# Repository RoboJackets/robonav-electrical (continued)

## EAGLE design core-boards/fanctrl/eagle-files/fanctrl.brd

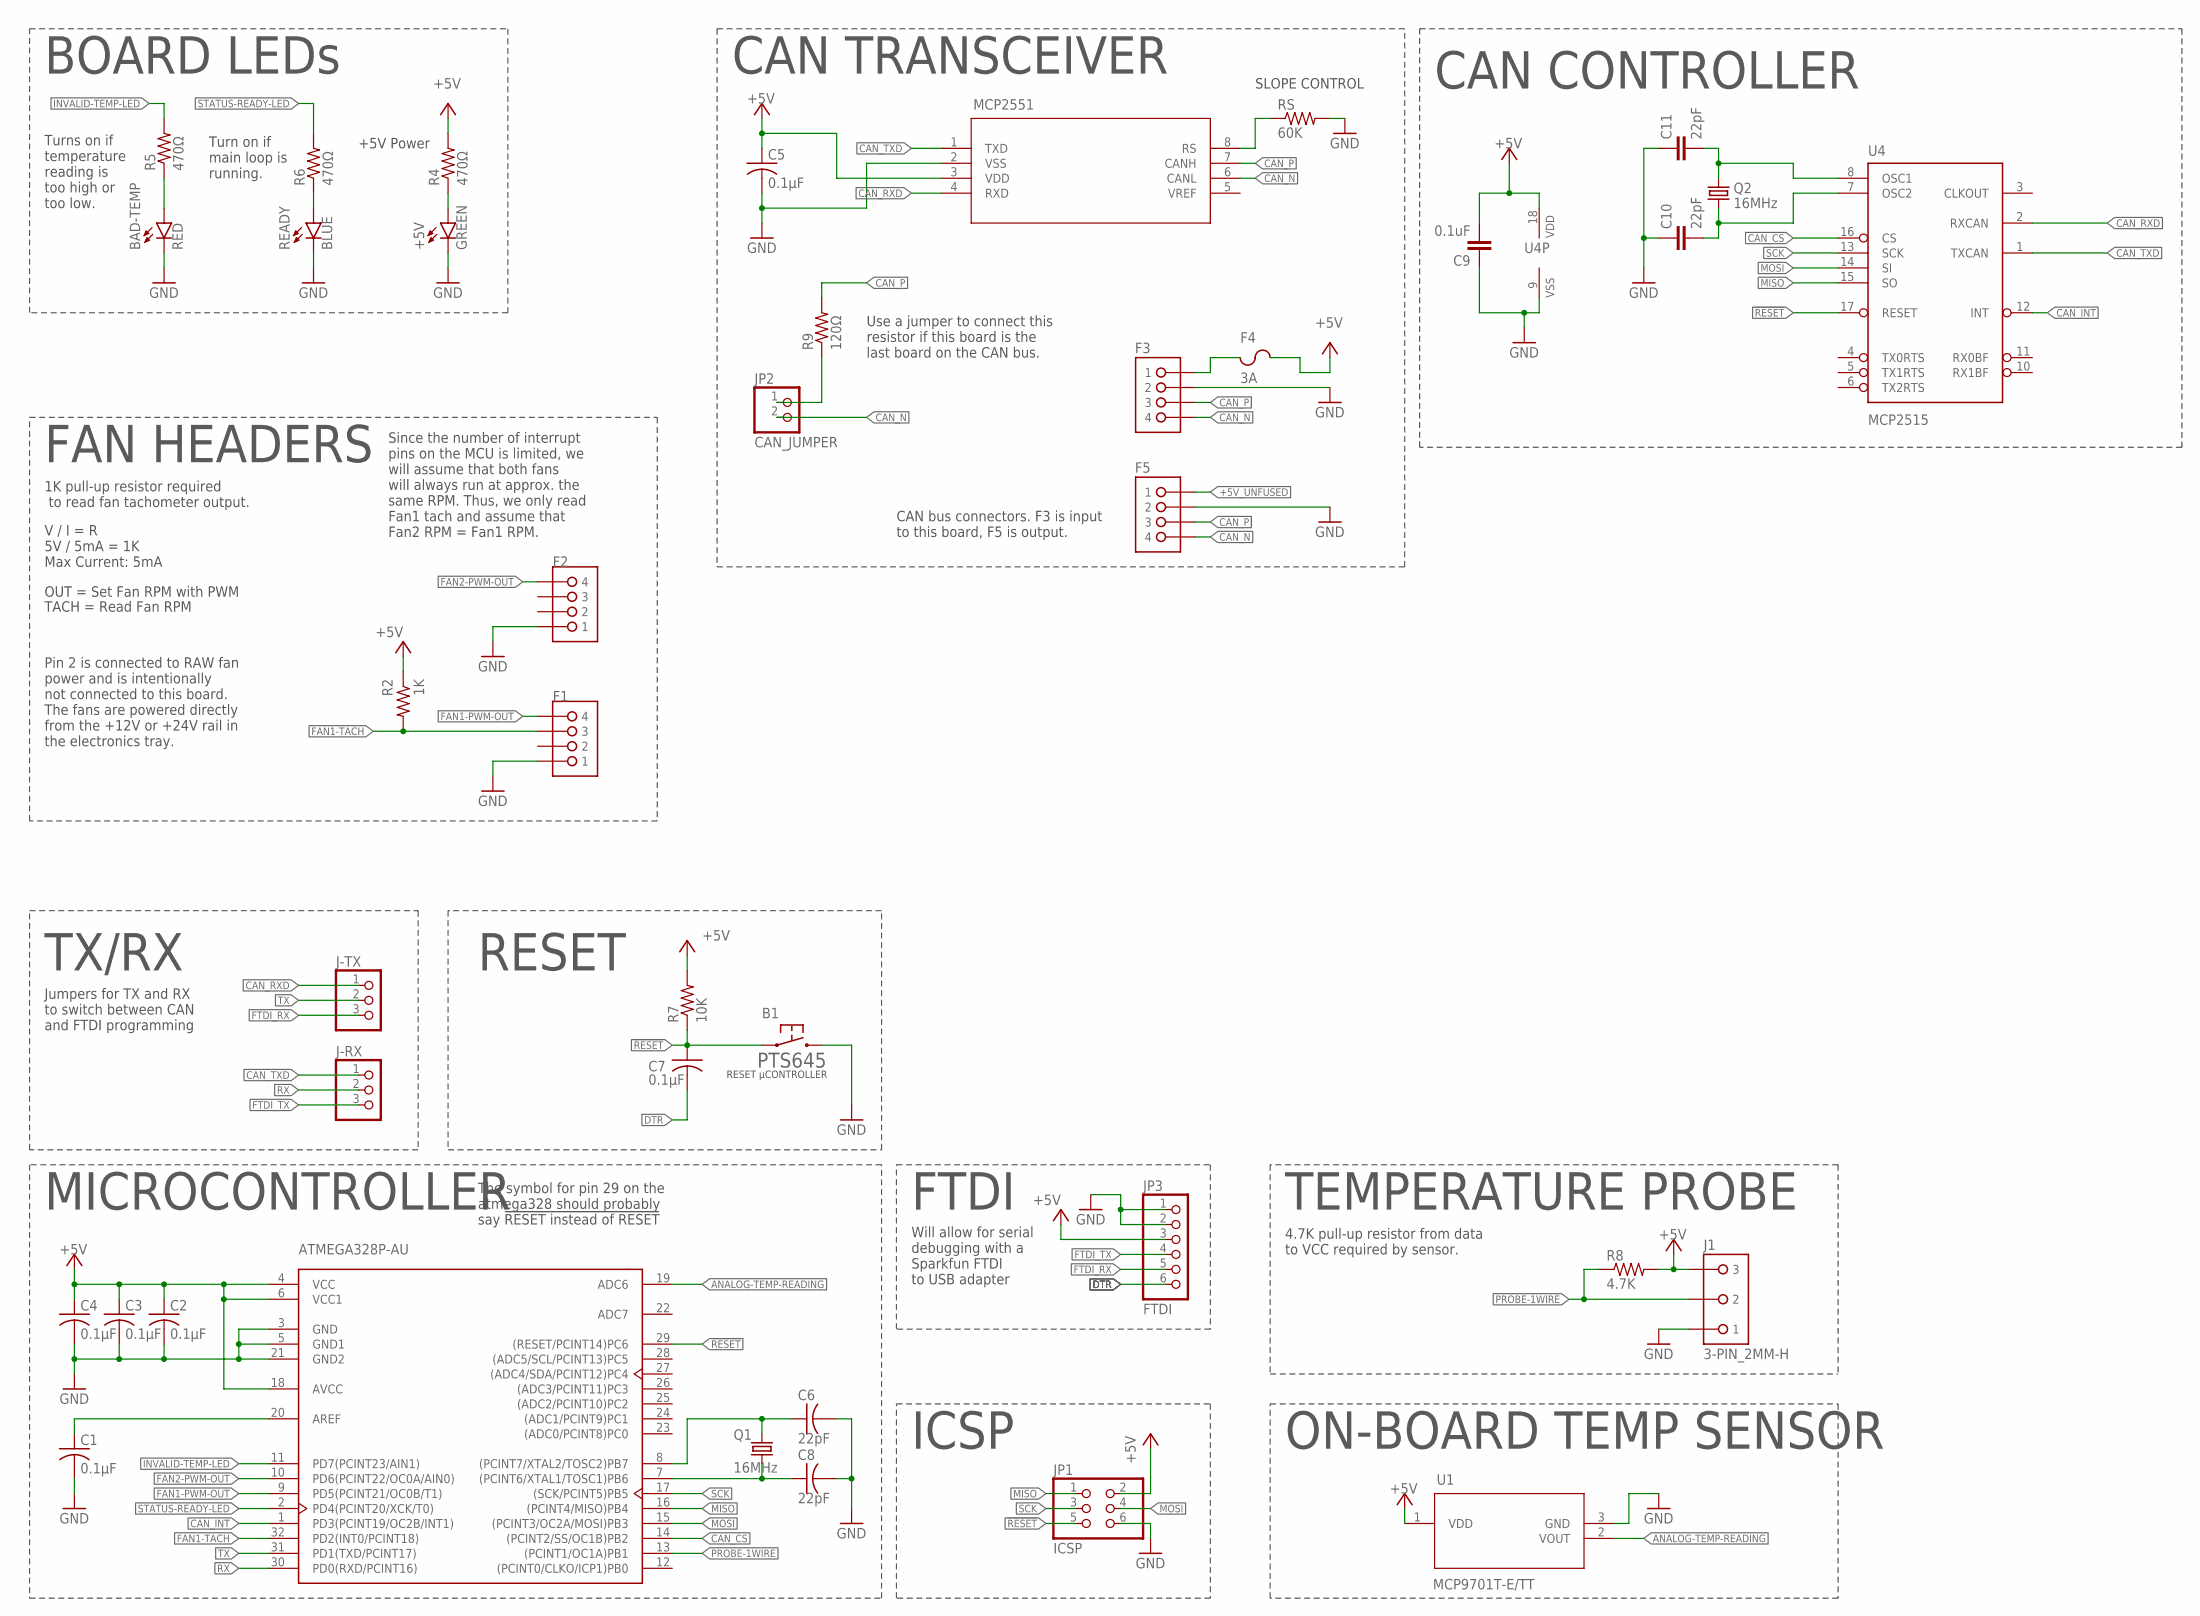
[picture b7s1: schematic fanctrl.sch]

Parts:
+5V: GREEN; CHIPLED_0603
ATMEGA328: ATMEGA328P-AU; TQFP-32
B1: PTS645
BAD-TEMP: RED; CHIPLED_0603
C1, C2, C3, C4, C5, C7: 0.1µF; C0603
C6, C8: 22pF; C0603
C9: 0.1uF; 0603-CAP
C10, C11: 22pF; 0603-CAP
F1, F2, F3, F5: 4-PIN_2MM-H; 2MM-4-H
F4: 3A; F1206
J1: 3-PIN_2MM-H; 2MM-3-H
J-RX: PINHD-1X3; 1X03
J-TX: PINHD-1X3; 1X03
JP1: ICSP; 2X03
JP2: CAN_JUMPER; 1X02
JP3: FTDI; 1X06/90
MCP2551: MCP2551T-I/SN; SOIC8-N_MC
Q1, Q2: 16MHz; CRYSTAL-SMD-5X3
R2: 1K; R0603
R4, R5, R6: 470Ω; R0603
R7: 10K; R0603
R8: 4.7K; R0603
R9: 120Ω; R0603
READY: BLUE; CHIPLED_0603
RS: 60K; R0603
U1: MCP9701T-E/TT; SOT-23_MC
U4: MCP2515; SO-18W

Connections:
!RESET: ATMEGA328.29 ((RESET/PCINT14)PC6), B1.P$1 (1), B1.P$2 (1), C7.1, JP1.5, R7.1, U4.17 (RESET)
+5V: ATMEGA328.4 (VCC), ATMEGA328.6 (VCC1), ATMEGA328.18 (AVCC), C2.1, C3.1, C4.1, C5.1, C9.2, F4.2, JP1.2, JP3.3, MCP2551.3 (VDD), R2.1, R4.2, R7.2, U1.1 (VDD), U4.18 (VDD)
+5V_UNFUSED: F3.1, F4.1, F5.1
ANALOG-TEMP-READING: ATMEGA328.19 (ADC6), U1.2 (VOUT)
AREF: ATMEGA328.20 (AREF), C1.1
CAN_CS: ATMEGA328.14 ((PCINT2/SS/OC1B)PB2), U4.16 (CS)
CAN_INT: ATMEGA328.1 (PD3(PCINT19/OC2B/INT1)), U4.12 (INT)
CAN_N: F3.4, F5.4, JP2.2, MCP2551.6 (CANL)
CAN_P: F3.3, F5.3, MCP2551.7 (CANH), R9.2
CAN_RS: MCP2551.8 (RS), RS.1
CAN_RXD: J-TX.1, MCP2551.4 (RXD), U4.2 (RXCAN)
CAN_TXD: J-RX.1, MCP2551.1 (TXD), U4.1 (TXCAN)
DTR: C7.2, JP3.6
FAN1-PWM-OUT: ATMEGA328.9 (PD5(PCINT21/OC0B/T1)), F1.4
FAN1-TACH: ATMEGA328.32 (PD2(INT0/PCINT18)), F1.3, R2.2
FAN2-PWM-OUT: ATMEGA328.10 (PD6(PCINT22/OC0A/AIN0)), F2.4
FTDI_RX: J-TX.3, JP3.5
FTDI_TX: J-RX.3, JP3.4
GND: +5V.C, ATMEGA328.3 (GND), ATMEGA328.5 (GND1), ATMEGA328.21 (GND2), B1.P$3 (2), B1.P$4 (2), BAD-TEMP.C, C1.2, C2.2, C3.2, C4.2, C5.2, C6.2, C8.2, C9.1, C10.1, C11.1, F1.1, F2.1, F3.2, F5.2, J1.1, JP1.6, JP3.1, JP3.2, MCP2551.2 (VSS), READY.C, RS.2, U1.3 (GND), U4.9 (VSS)
INVALID-TEMP-LED: ATMEGA328.11 (PD7(PCINT23/AIN1)), R5.2
MISO: ATMEGA328.16 ((PCINT4/MISO)PB4), JP1.1, U4.15 (SO)
MOSI: ATMEGA328.15 ((PCINT3/OC2A/MOSI)PB3), JP1.4, U4.14 (SI)
unnamed: ATMEGA328.7 ((PCINT6/XTAL1/TOSC1)PB6), C8.1, Q1.1
unnamed: J1.3, R8.2
unnamed: +5V.A, R4.1
unnamed: BAD-TEMP.A, R5.1
unnamed: R6.1, READY.A
unnamed: ATMEGA328.8 ((PCINT7/XTAL2/TOSC2)PB7), C6.1, Q1.3 (2)
unnamed: C11.2, Q2.3 (2), U4.8 (OSC1)
unnamed: C10.2, Q2.1, U4.7 (OSC2)
PROBE-1WIRE: ATMEGA328.13 ((PCINT1/OC1A)PB1), J1.2, R8.1
RX: ATMEGA328.30 (PD0(RXD/PCINT16)), J-RX.2
R_JUMPER: JP2.1, R9.1
SCK: ATMEGA328.17 ((SCK/PCINT5)PB5), JP1.3, U4.13 (SCK)
STATUS-READY-LED: ATMEGA328.2 (PD4(PCINT20/XCK/T0)), R6.2
TX: ATMEGA328.31 (PD1(TXD/PCINT17)), J-TX.2

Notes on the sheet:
MICROCONTROLLER
BOARD LEDs
RESET
CAN TRANSCEIVER
FAN HEADERS
TEMPERATURE PROBE
ON-BOARD TEMP SENSOR
4.7K pull-up resistor from data to VCC required by sensor.
1K pull-up resistor required to read fan tachometer output.
The symbol for pin 29 on the atmega328 should probably say !RESET instead of RESET
V / I = R 5V / 5mA = 1K Max Current: 5mA
ICSP
OUT = Set Fan RPM with PWM
TACH = Read Fan RPM
Use a jumper to connect this resistor if this board is the last board on the CAN bus.
CAN bus connectors. F3 is input to this board, F5 is output.
Pin 2 is connected to RAW fan power and is intentionally not connected to this board. The fans are powered directly from the +12V or +24V rail in the electronics tray.
+5V Power
Turns on if temperature reading is too high or too low.
Turn on if main loop is running.
FTDI
SLOPE CONTROL
TX/RX
CAN CONTROLLER
Jumpers for TX and RX to switch between CAN and FTDI programming
Will allow for serial debugging with a Sparkfun FTDI to USB adapter
Since the number of interrupt pins on the MCU is limited, we will assume that both fans will always run at approx. the same RPM. Thus, we only read Fan1 tach and assume that Fan2 RPM = Fan1 RPM.

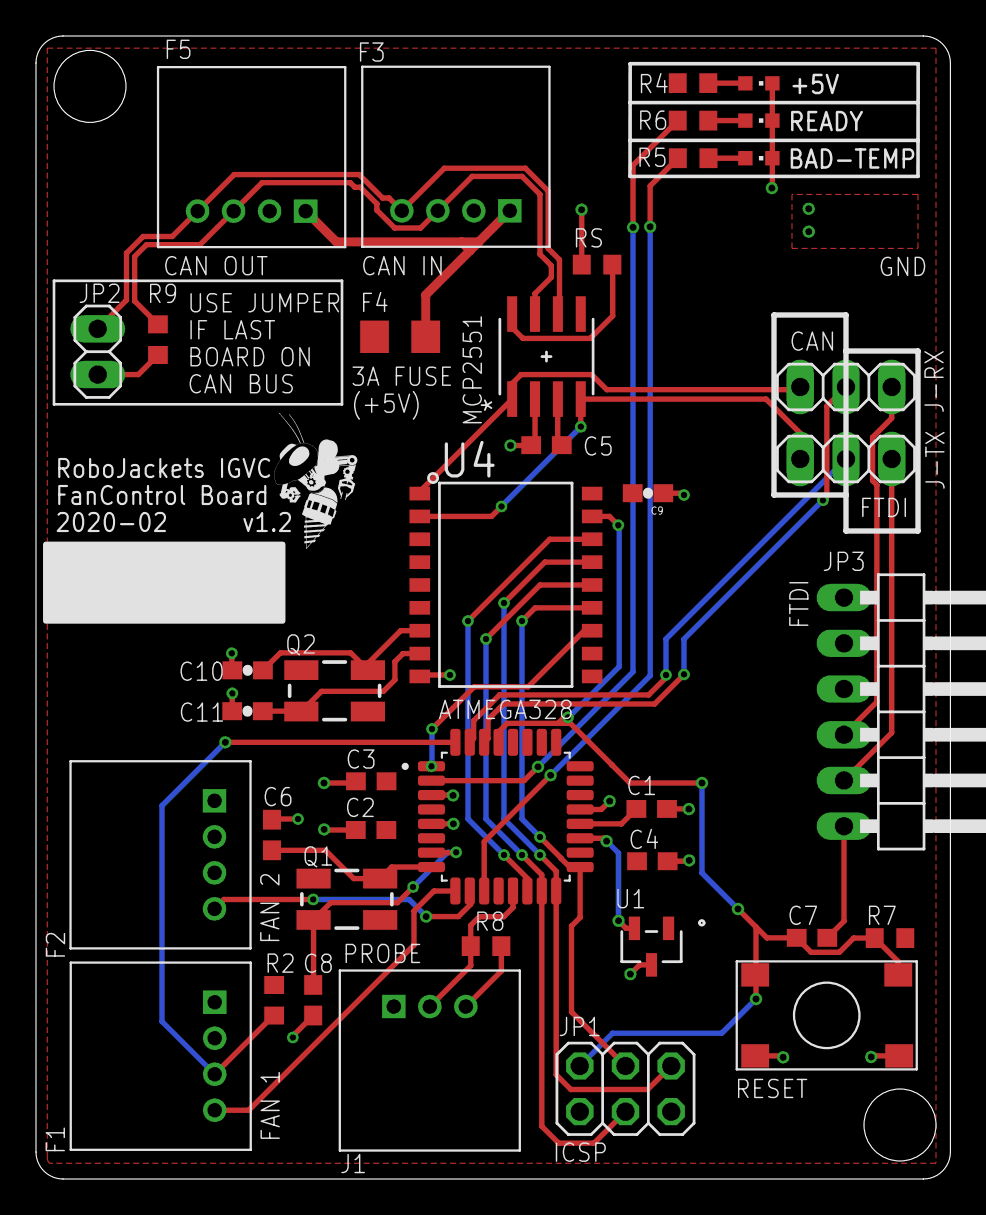
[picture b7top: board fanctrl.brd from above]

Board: 2 copper layers, 50.8 x 63.5 mm, 41 parts (0 on the bottom side), 36 nets.

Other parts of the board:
U$1: ROBOBUZZ_0.4X

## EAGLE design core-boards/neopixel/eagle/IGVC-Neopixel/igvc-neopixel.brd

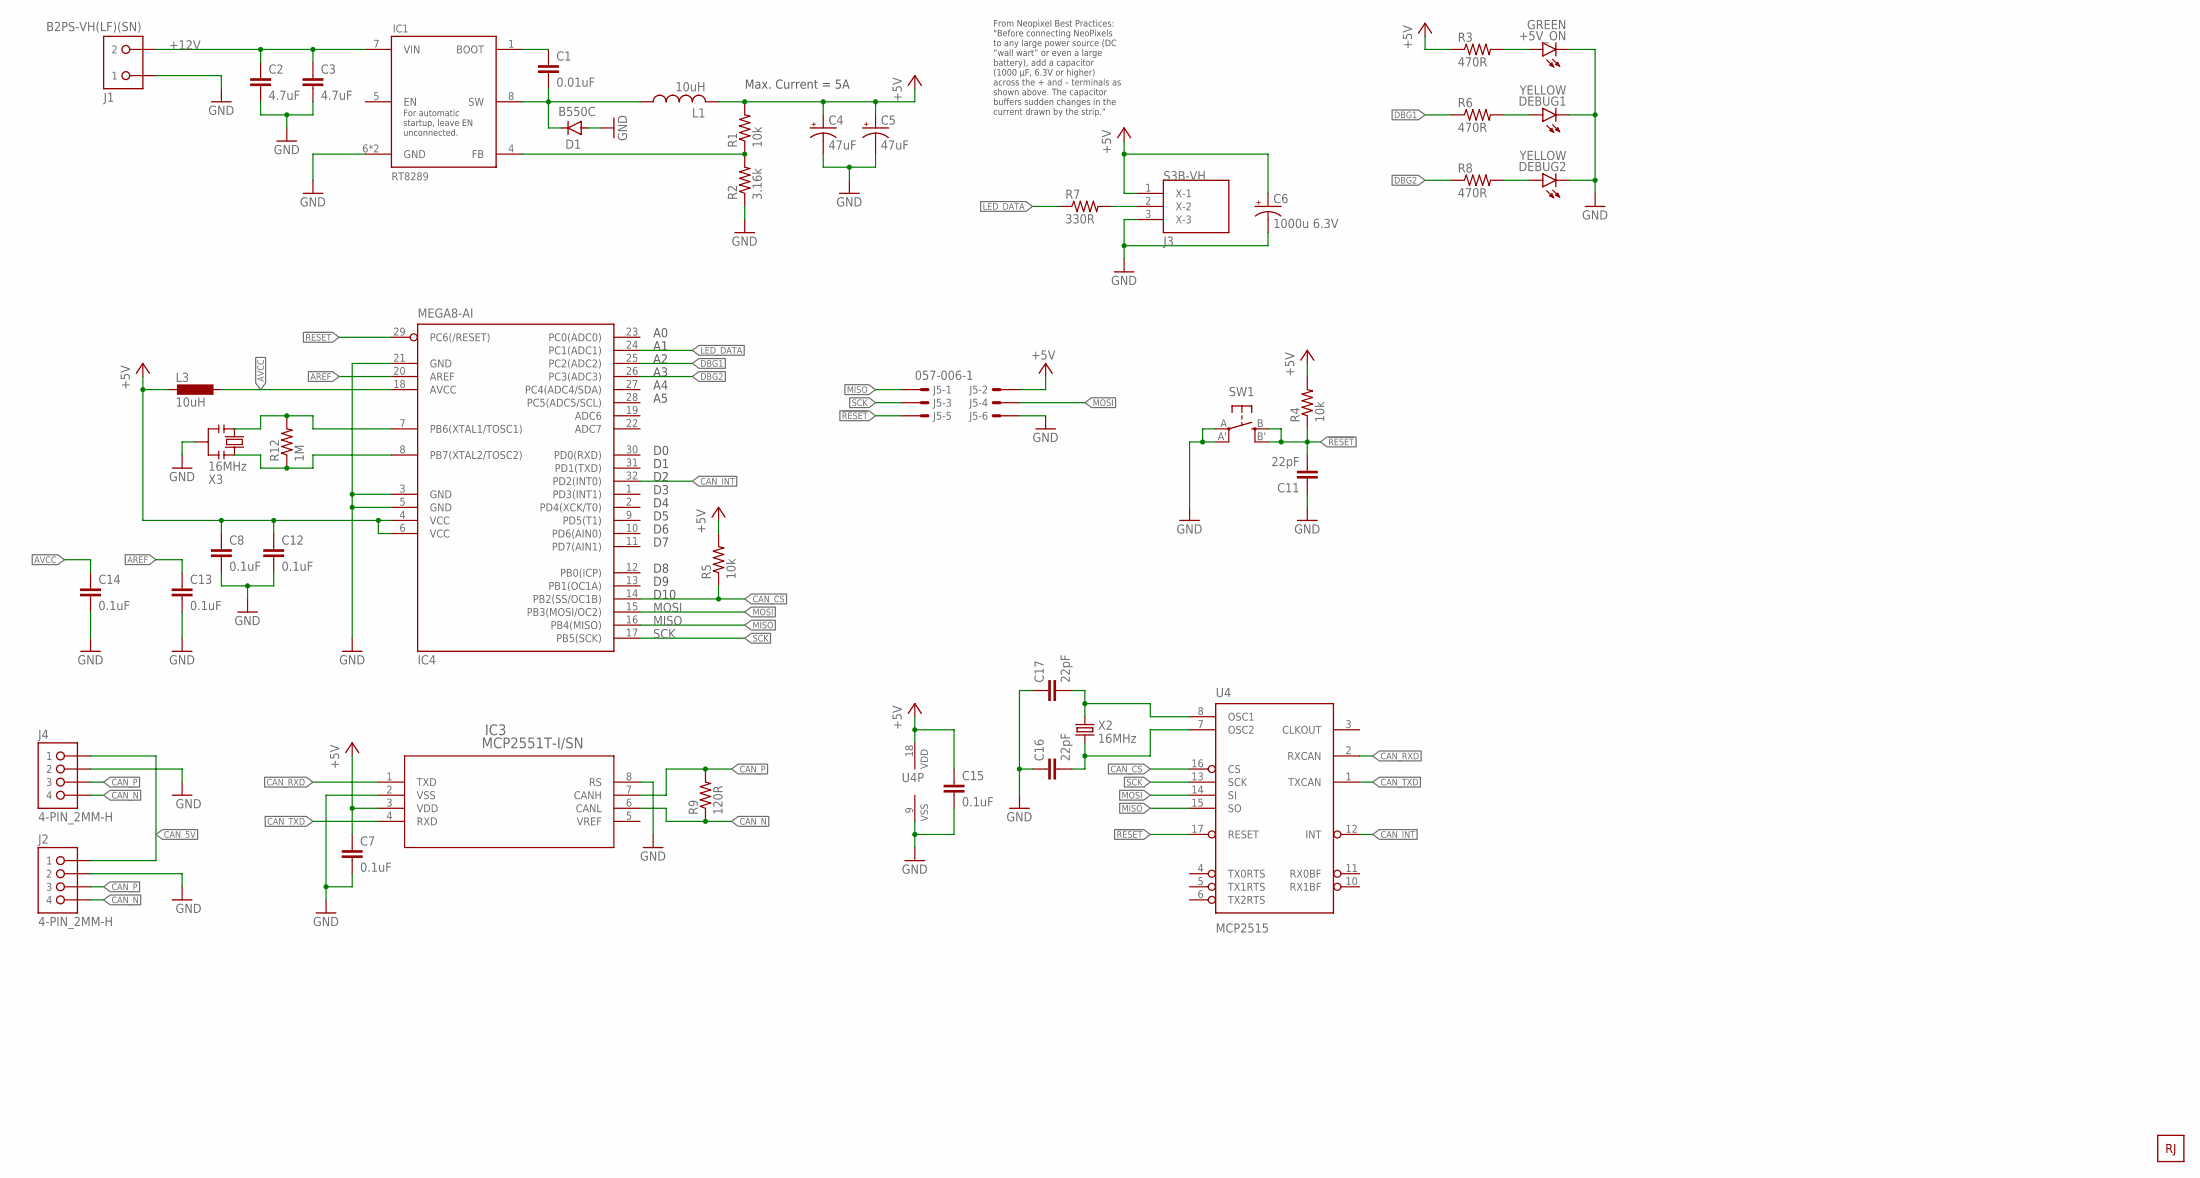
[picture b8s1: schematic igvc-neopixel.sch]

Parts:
+5V_ON: GREEN; CHIP-LED0805; DIGIKEY 732-4982-1-ND
C1: 0.01uF; C0603; DIGIKEY 311-1572-1-ND
C2, C3: 4.7uF; C1206; DIGIKEY 1276-3178-1-ND
C4, C5: 47uF; E5-10,5; DIGIKEY PCE3753CT-ND
C6: 1000u 6.3V; E5-10,5; DIGIKEY 493-2160-1-ND
C7, C8, C12, C13, C14: 0.1uF; C0603; DIGIKEY 399-1099-1-ND
C11: 22pF; C0603; DIGIKEY 311-3952-1-ND
C15: 0.1uF; C0603
C16, C17: 22pF; C0603; DIGIKEY 399-1099-1-ND
D1: B550C; SMC; DIGIKEY B550C-FDICT-ND
DEBUG1, DEBUG2: YELLOW; CHIP-LED0805; DIGIKEY 732-4987-1-ND
IC1: RT8289; SOIC8_EP; DIGIKEY 1028-1046-1-ND
IC3: MCP2551T-I/SN; SOIC8-N_MC; DIGIKEY MCP2551T-I/SNCT-ND
IC4: MEGA8-AI; TQFP32-08; DIGIKEY ATMEGA328P-AURCT-ND
J1: B2PS-VH(LF)(SN); B2PS-CENTERED
J2, J4: 4-PIN_2MM-H; 2MM-4-H
J3: S3B-VH; DIGIKEY 455-1649-ND
J5: 057-006-1; DIGIKEY 3M15451-ND
L1: 10uH; SRR1208; DIGIKEY SRR1208-100MLCT-ND
L3: 10uH; 0805; DIGIKEY 490-1053-1-ND
R1, R4: 10k; R0603; DIGIKEY RNCP0603FTD10K0CT-ND
R2: 3.16k; R0603; DIGIKEY RMCF0603FT3K16CT-ND
R3, R6, R8: 470R; R0603; DIGIKEY RMCF0603JT470RCT-ND
R5: 10k; R0603
R7: 330R; R0603; DIGIKEY RMCF0603JT330RCT-ND
R9: 120R; R0603; DIGIKEY RMCF0603JT120RCT-ND
R12: 1M; R0603; DIGIKEY 311-1.00MHRCT-ND
SW1: SPST_TACT-EVQQ2; EVQ-Q2; DIGIKEY P12961SCT-ND
U4: MCP2515; SO-18W
U$1: ROBOBUZZ0.6X; ROBOBUZZ_0.6X
X2: 16MHz; CRYSTAL-SMD-5X3
X3: 16MHz; RESONATOR; DIGIKEY 490-17948-1-ND

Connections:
!RESET: C11.2, IC4.29 (PC6(/RESET)), J5.5, R4.1, SW1.B (S), SW1.B' (S1), U4.17 (RESET)
+5V: C4.+, C5.+, C6.+, C7.1, C8.1, C12.1, C15.1, IC3.3 (VDD), IC4.4 (VCC), IC4.6 (VCC), J3.1 (X-1), J5.2, L1.2, L3.2, R1.2, R3.1, R4.2, R5.2, U4.18 (VDD)
+12V: C2.1, C3.1, IC1.7 (VIN), J1.2
AREF: C13.1, IC4.20 (AREF)
AVCC: C14.1, IC4.18 (AVCC), L3.1
BOOT: C1.1, IC1.1 (BOOT)
CAN_5V: J2.1, J4.1
CAN_CS: IC4.14 (PB2(SS/OC1B)), R5.1, U4.16 (CS)
CAN_INT: IC4.32 (PD2(INT0)), U4.12 (INT)
CAN_N: IC3.6 (CANL), J2.4, J4.4, R9.1
CAN_P: IC3.7 (CANH), J2.3, J4.3, R9.2
CAN_RXD: IC3.1 (TXD), U4.2 (RXCAN)
CAN_TXD: IC3.4 (RXD), U4.1 (TXCAN)
DBG1: IC4.25 (PC2(ADC2)), R6.1
DBG2: IC4.26 (PC3(ADC3)), R8.1
FB: IC1.4 (FB), R1.1, R2.2
GND: +5V_ON.C, C2.2, C3.2, C4.-, C5.-, C6.-, C7.2, C8.2, C11.1, C12.2, C13.2, C14.2, C15.2, C16.1, C17.1, D1.A, DEBUG1.C, DEBUG2.C, IC1.6 (GND), IC1.EXP (GND), IC3.2 (VSS), IC3.8 (RS), IC4.3 (GND), IC4.5 (GND), IC4.21 (GND), J1.1, J2.2, J3.3 (X-3), J4.2, J5.6, R2.1, SW1.A, SW1.A' (P1), U4.9 (VSS), X3.2
LED_DATA: IC4.24 (PC1(ADC1)), R7.1
MISO: IC4.16 (PB4(MISO)), J5.1, U4.15 (SO)
MOSI: IC4.15 (PB3(MOSI/OC2)), J5.4, U4.14 (SI)
unnamed: C17.2, U4.8 (OSC1), X2.3 (2)
unnamed: C16.2, U4.7 (OSC2), X2.1
NEOPIXEL: J3.2 (X-2), R7.2
PWR_LED: +5V_ON.A, R3.2
SCK: IC4.17 (PB5(SCK)), J5.3, U4.13 (SCK)
STAT1_LED: DEBUG1.A, R6.2
STAT2_LED: DEBUG2.A, R8.2
SW: C1.2, D1.C, IC1.8 (SW), L1.1
XTAL1: IC4.7 (PB6(XTAL1/TOSC1)), R12.2, X3.1
XTAL2: IC4.8 (PB7(XTAL2/TOSC2)), R12.1, X3.3

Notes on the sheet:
D10
Max. Current = 5A
From Neopixel Best Practices: "Before connecting NeoPixels to any large power source (DC “wall wart” or even a large battery), add a capacitor (1000 µF, 6.3V or higher) across the + and – terminals as shown above. The capacitor buffers sudden changes in the current drawn by the strip."
For automatic startup, leave EN unconnected.

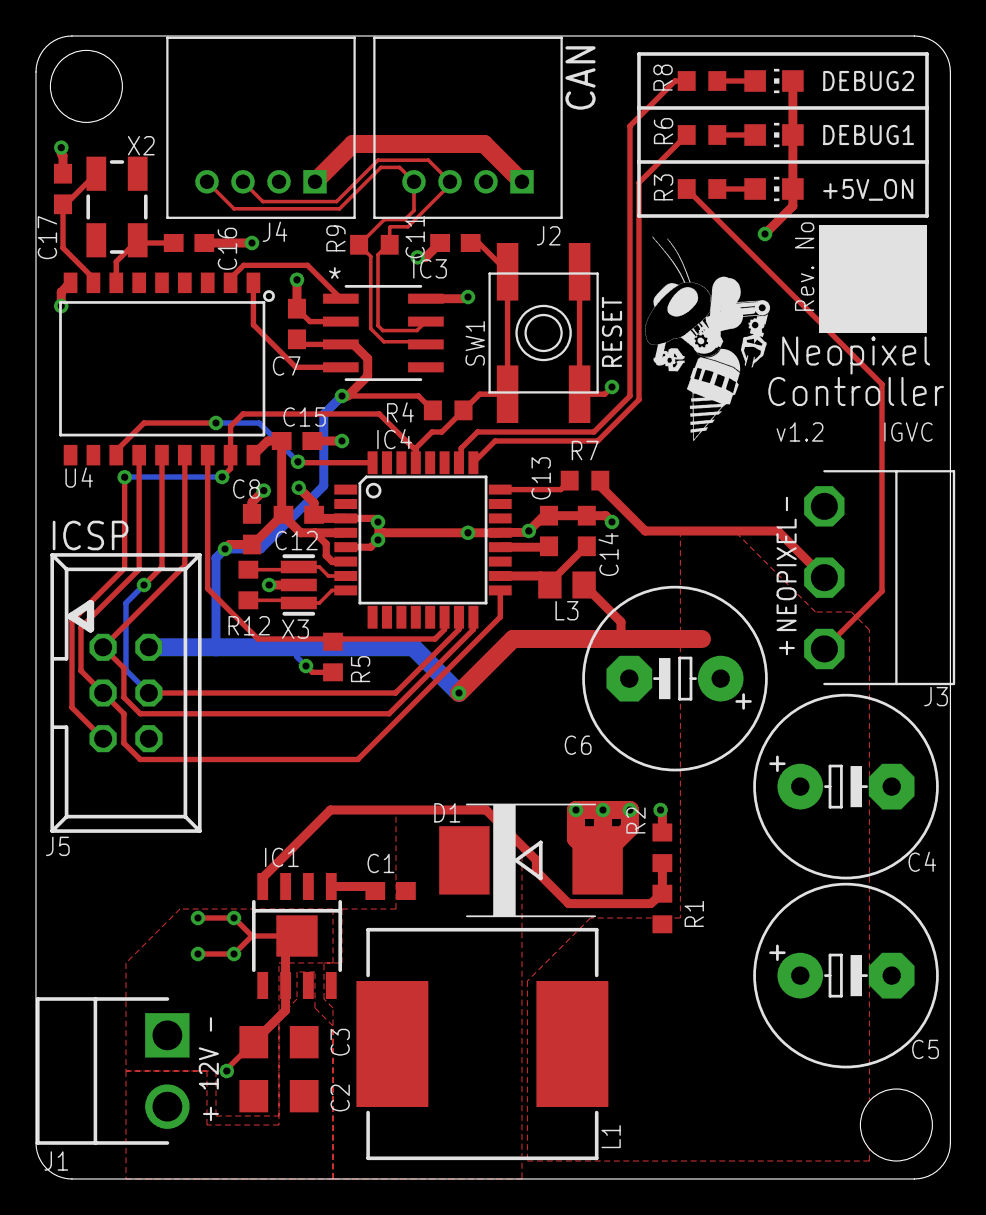
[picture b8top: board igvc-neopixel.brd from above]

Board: 2 copper layers, 50.8 x 63.5 mm, 44 parts (0 on the bottom side), 30 nets.

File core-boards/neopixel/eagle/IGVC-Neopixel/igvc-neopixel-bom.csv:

"Qty","Value","Device","Package","Parts","Description","CASE","DIGIKEY","MANUFACTURER_PART_NUMBER","MF","MONTHLY_USAGE","MPN","OC_FARNELL","OC_NEWARK","PART_NUMBER","POPULARITY","PRICE","SPICEPREFIX","SUPPLIER","TYPE","VALUE","VENDOR",
"1","0.01uF","C-EUC0603","C0603","C1","CAPACITOR, European symbol","","311-1572-1-ND","","","","","","","","","","","","","","",
"1","0.1uF","C-EUC0603","C0603","C7","CAPACITOR, European symbol","","399-1099-1-ND","","","","","","","","73","","C","","","","",
"4","0.1uF","C-EUC0603","C0603","C8, C12, C13, C14","CAPACITOR, European symbol","","399-1099-1-ND","","","","","","","","","","","","","","",
"1","057-006-1","057-006-1","057-006-1","J5","CONNECTOR","","3M15451-ND","","","","","unknown","unknown","","0","","","","","","",
"1","1000u 6.3V","CPOL-USE","PANASONIC_E","C6","POLARIZED CAPACITOR, American symbol","","493-2160-1-ND","","","","","","","","","","","","","","",
"2","10K","R-US_R0603","R0603","R1, R4","RESISTOR, American symbol","","RNCP0603FTD10K0CT-ND","","","","","","","","","","","","","","",
"1","10uH","L-0805","0805","L3","","","490-1053-1-ND","","","","","","","","","","","","","","",
"1","10uH","SRR1208","SRR1208","L1","","","SRR1208-100MLCT-ND","","","","","","","","","","","","","","",
"2","120R","R-US_R0603","R0603","R9, R10","RESISTOR, American symbol","","RMCF0603JT120RCT-ND","","","","","","","","77","","R","","","","",
"1","16MHz","OSC_CSTCE16M0V53-R0","RESONATOR","X3","16Mhz - SMD","","490-17948-1-ND","","","_____","","","","CSTCE16M0V53-R0","","_____","","_____","Cristalli","CSTCE16M0V53-R0","",
"1","1M","R-US_R0603","R0603","R12","RESISTOR, American symbol","","311-1.00MHRCT-ND","","","","","","","","","","","","","","",
"1","22pF","C-EUC0603","C0603","C11","CAPACITOR, European symbol","","311-3952-1-ND","","","","","","","","","","","","","","",
"1","3.16K","R-US_R0603","R0603","R2","RESISTOR, American symbol","","RMCF0603FT3K16CT-ND","","","","","","","","","","","","","","",
"1","330R","R-US_R0603","R0603","R7","RESISTOR, American symbol","","RMCF0603JT330RCT-ND","","","","","","","","77","","R","","","","",
"2","4-PIN_2MM-H","4-PIN_2MM-H","2MM-4-H","J2, J4","MPN: 0353630460","","WM18933-ND","","","","0353630460","","","","","","","","","","",
"2","4.7uF","C-EUC1206","C1206","C2, C3","CAPACITOR, European symbol","","1276-3178-1-ND","","","","","","","","","","","","","","",
"3","470R","R-US_R0603","R0603","R3, R6, R8","RESISTOR, American symbol","","RMCF0603JT470RCT-ND","","","","","","","","","","","","","","",
"2","47uF","CPOL-USD","PANASONIC_D","C4, C5","POLARIZED CAPACITOR, American symbol","","PCE3753CT-ND","","","","","","","","","","","","","","",
"1","B2PS-VH(LF)(SN)","B2PS-VH(LF)(SN)","B2PS-CENTERED","J1","Power Connector","","455-1648-ND","","","","B2PS-VH(LF)(SN)","","","","","","","","","","",
"1","B550C","DIODE-SMC","SMC","D1","DIODE","","B550C-FDICT-ND","","","","","","","","1","","","","","","",
"1","GREEN","LEDCHIP-LED0805","CHIP-LED0805","ON","LED","","732-4982-1-ND","","","","","","","","68","","","","","","",
"1","MCP2551T-I/SN","MCP2551T-I/SN","SOIC8-N_MC","IC3","","","MCP2551T-I/SNCT-ND","MCP2551TISN","","","","","","","","","","","","","Microchip",
"1","MEGA8-AI","MEGA8-AI","TQFP32-08","IC4","MICROCONTROLLER","","ATMEGA328P-AURCT-ND","","","","ATMEGA8-16AU","9171371","73M8863","","11","","","","","","",
"1","ROBOBUZZ1.0X","ROBOBUZZ1.0X","ROBOBUZZ_1.0X","U$1","","","","","","","","","","","","","","","","","",
"1","RT8289","RT8289","SOIC8_EP","IC1","","","1028-1046-1-ND","","","","","","","","","","","","","","",
"1","S3B-VH","S3B-VH","S3B-VH","J3","","","455-1649-ND","","","","","","","","","","","","","","",
"1","SPST_TACT-EVQQ2","SPST_TACT-EVQQ2","EVQ-Q2","SW1","SMT 6mm switch, EVQQ2 series","","P12961SCT-ND","","","","","","","","","","","","","","",
"2","YELLOW","LEDCHIP-LED0805","CHIP-LED0805","DEBUG1, DEBUG2","LED","","732-4987-1-ND","","","","","","","","68","","","","","","",

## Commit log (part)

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2018-03-11 Estop Fixed
2018-03-13 Indentation Correction and Clean up#
2018-03-25 added editorconfig to repo
2018-03-29 Bug fixes and magic compilatoin
2018-04-01 Magic
2018-04-04 Upload
2018-04-08 Update working code
2018-04-10 PID fixed, also wrote a PID testbench
2018-04-10 I of PID added, just for testing purposes so far
2018-04-11 fixed motors going backwards on positive speeds
2018-04-11 added I to be set at run time
2018-04-13 Minor grammar changes
2018-04-15 Revise estop code
2018-04-22 Remove toggle mode in estop
2018-05-20 added safety light code
2018-05-28 added timer reset for mbed timer
2018-09-23 fix radio pins, add labels
2018-09-27 changed motorboard folder to lgic
2018-09-27 motor -> logic
2018-09-27 added ACS711 device
2018-09-27 added MIC29301 devices
2018-09-27 added various components
2018-09-27 added safety light power
2018-09-28 added more power and removed old circuits
2018-09-30 added discrete library
2018-09-30 added atmega328 lbr
2018-10-08 Working on the Schematic for a BareBones Arduino
2018-10-11 added new imu
2018-10-11 removed imu
2018-10-11 created wireless
2018-10-11 moved libraries
2018-10-11 added BMI088 to lbr
2018-10-11 added IMU to wireless
2018-10-12 removed IMU from sch
2018-10-14 Wired Board
2018-10-28 Update to LED board
2018-11-01 ethernet comm implementation initial commit. Compiles but DOES NOT work yet
2018-11-04 Ethernet works
2018-12-02 fixes
2018-12-12 remove client.close() statements and reset buffer within nested while(true) loop
2018-12-13 clear buffer to prevent overflow issues. Format debugging info. Abstract parseNonMotor to helper method
2019-01-12 further reduce value of TIMEOUT_MS, update comments
2019-01-13 Cleaning LED Schematic + Board
2019-01-13 New relay estop
2019-01-18 add protobuf msgs and include into main script
2019-01-18 Fixing Board Errors
2019-01-19 added nanopb repo and compile scripts in mbed-libs. Cleaned up main.cpp
2019-01-19 added nanopb submodule
2019-01-20 finish modifying main.cpp
2019-01-21 fixing schematic
2019-01-24 Estop routingstarted
2019-01-25 Labels Cleared
2019-01-25 added atmega2560
2019-01-26 estop board - not completely finished...
2019-01-26 Fin touches, swapped 5 pin connector
2019-01-26 Aesthetics changes wrt scc design review guideline
2019-01-27 Minor changes
2019-01-27 add logic to stop motors when client disconnects
2019-01-27 reset estop logic when client reconnects
2019-01-27 added led control
2019-01-27 added logic board connector
2019-02-10 Reorganzing the Schematic and adding documentation
2019-02-17 Documentation + style changes
2019-02-19 estop diode magic
2019-02-19 Revert "estop diode magic"
    This reverts commit 0d0471845709adb358787b62836d6b2af97c87b1.
2019-02-19 Added notes + redid ATMEGA328p chip
2019-02-19 Logic board edit, connector spec-ed, battery voltage functionality removed and Lidar added
2019-02-22 Connector between Motor board and Diagnostic board
2019-02-23 Adding sensor curcuits and working on serial
2019-02-23 Library upload
2019-02-23 added hotswap connector
2019-02-23 Added Hotswap Components
2019-02-23 DesignReviewReady
2019-02-23 addition of current sensor + microsd + temparature sensor
2019-02-23 Hotswap Board
2019-02-23 added connector
2019-02-25 Cleaned up
2019-02-25 Internal design review logic brd
2019-03-01 Switched labels to tags and finished micro sd sensor
2019-03-02 Logic board edit complete w/out IMA198
2019-03-02 Hotswap Design Review (Asha)
2019-03-03 Finishing Touches
2019-03-03 Label changes and bidirection logic shifter added
2019-03-03 Final Touches
2019-03-03 design review
2019-03-03 fixed boundaries
2019-03-03 wireless fixes
2019-03-03 wireless review notes
2019-03-04 fixed radio header
2019-03-05 Fix capacitors
2019-03-05 Post design review changes
2019-03-05 Routing Complete, pending label creation
2019-03-09 Bosch IMU added
2019-03-11 fixes from design review
2019-03-11 Hotswap Post Design Review
2019-03-11 Finished Design Review Changes
2019-03-11 Renamed to Diagnostic
2019-03-11 Hotswap Final
2019-03-12 Started on the board
2019-03-18 Changed derivative and integral calculations.
2019-03-19 Added low pass to derivative and clamping on integral
2019-03-20 Finished incompleted comment
2019-03-21 Removed constexpr since not c++11
2019-03-25 Finishing touches with board layout
2019-04-07 Board functionally done, just need to make it look better
2019-04-08 board revisions v1
2019-04-12 Fixed Airwires
2019-04-16 Updated pins for jessii
2019-05-24 Added Kv to protobuf message.
2019-05-25 Updated estop pin to 15
2019-05-25 Flipped estop if
2019-06-01 new estop code
2019-06-02 fixed estop code
2019-06-08 fix silkscreen
2019-06-10 Integral clamp calculation
2019-06-10 added LED light indicators
2019-07-23 restructure
2019-08-25 Flip transistor sides so voltage does not reverse flow from V2 to V1 when V2 is higher
2019-10-27 Created fan control schematic file.
2019-10-27 Schematic
2019-10-27 Neopixel board
2019-11-03 Created Connector Part
2019-11-03 Improve schematic layout and correct power/gnd symbols.
2019-11-04 Initial layout inside RoboJackets frame.
2019-11-07 logic board revision schemaitcs done
2019-11-10 logic board design for internal review :rocket:
2019-11-10 estop before internal
2019-11-10 Pin inversion fix
2019-11-10 Add CAN controller footprint/part (MCP2551) to IGVC-Microcontroller lbr.
2019-11-10 Add LEDs (power, error, ready) and reset button.
2019-11-10 design rev
2019-11-10 Add lbr for 5pin CAN connector (JST_XH).
2019-11-10 Added new connector
2019-11-10 Add CAN Controller (Module, Connector) to schematic. Label schematic sub-systems.
2019-11-10 Added Devices
2019-11-14 Internal Design Review Changes
2019-11-15 More small changes
2019-11-16 estop tx design review
2019-11-16 changes before design rev
2019-11-16 fixed 5v airwire
2019-11-17 Fix CAN signal names for automatic differential routing.
2019-11-17 Updated the Reset Button.
2019-11-17 Adjust board size to 2in.
2019-11-17 More changes
2019-11-17 11/17/19 I fixed the issues
2019-11-17 Routed the Board
2019-11-17 Very rough start to board layout.
2019-11-17 mend
2019-11-17 20191117 Reworked schematic
2019-11-17 finished schematics
2019-11-22 More Design Review Changes
2019-11-24 Add pull-up resistor for temp probe; add schematic documentation.
2019-11-24 11/24/19
    Organized Schematic
2019-11-25 Fix merge problem.
2019-11-30 Final Changes
2019-11-30 Revert "Final Changes"
    This reverts commit 7903053608bd51a5aa59f005e6dfdce4322bed2e.
2019-11-30 test
2019-12-01 Schematics rev Done
2019-12-01 Fixing connector type
2019-12-01 Added Mounting Holes
2019-12-02 change connector type
2019-12-02 almost order ready haha
2019-12-03 things should be done tm
2019-12-03 the ordered board :party-parrot
2019-12-03 adding dimensions
2020-01-09 Change CAN connector from 5 to 4 pin.
2020-01-11 1/11/2020
    Added CAN bus/connector and implemented SPI with LCDs
2020-01-12 Connected Airwires/Mount holes
2020-01-13 1/12/2020
    Switched out 100 pin ATmega for 32 pin, put in new connectors
2020-01-16 Added Can Module (Inncomplete)
2020-01-16 Fixed routing problems. Added some docu layer.
2020-01-19 Relayout neopixel schematic
2020-01-19 Finish Optisolators
2020-01-19 1/19/20
    Changed out transistors for resistors, did initial routing
2020-01-23 Redid component for LCD screen
    And broke entire board
2020-01-23 Routing neopixel
2020-01-23 Neopixel silkscreen
2020-01-23 finish schematic
2020-01-26 Revert "Update mast_panel_board.sch"
    This reverts commit efd99cb2754bcfe550521ba74416bc807029b3fb.
2020-01-26 Finishing touches to the board
2020-01-26 Changed 3-pin temp probe connector to 2MM-H, robojackets-connectors.
2020-01-26 1/26/20
    Added LEDs, new connector symbols. Started rerouting board.
2020-01-27 Minor tweaks
2020-02-02 Ran ratsnest followed by ripup @; to remove airwires for design review.
2020-02-02 Extraneous changes to remote display
2020-02-02 Rounded corners for neopixel board
2020-02-03 Fixed a wire in the neopixel schematic
2020-02-04 2/3/20
    Added labels and cleaned up some stuff
2020-02-06 Fix typo: ISCP --> ICSP.
2020-02-06 Internal review remote display
2020-02-06 Jank jumper for CAN resistor added.
2020-02-06 Add 3A fuse to +5V from CAN bus.
2020-02-06 One ground per power pin on the ATMega.
2020-02-06 Fix decoupling CAP locations.
2020-02-06 Fix connector orientation. Change fan signal names for less confusion.
2020-02-06 Change CAN controller name to MCP2551.
2020-02-06 Make RESET line routing nicer.
2020-02-06 Improve tPlace documentation.
2020-02-09 2/9/2020
    Cleaned up schematic, fixed pin assignments, added power plane and avr connector, changed resistor connection on CAN bus
2020-02-09 Added Second Can Connector
2020-02-12 Finished some stuff
2020-02-13 Add reminder to add text near CAN jumper.
2020-02-16 Add FTDI connector.
2020-02-16 Edited
2020-02-16 Fixed estop RX
2020-02-17 Re-route board to v1.1.
2020-02-17 Minor fixes: LED names, Probe-PWM signal name change to PROBE-1WIRE.
2020-02-17 Leave VREF pin on MCP2551 disconnected.
2020-02-19 Add crystal oscillator to ATMEGA328.
2020-02-19 Route crystal. Misc routing improvements. Improve +5V distribution on Top layer. Add silkscreen boxes.
2020-02-19 initial wiring diagram file
2020-02-20 Removed wrong version of BOM (correct version is on Google Drive)
2020-02-20 Fixed estop-tx
2020-02-25 2/23/19
    Changed out resistors, fixed SPI connections on board
2020-02-26 wiring diagram for basic system
2020-02-27 moving standoff holes from back in the day MotorBoardDev library
2020-02-27 Update currentSensingBoard.sch
    Added CAN controller, added program header.
2020-02-27 [v1.2] Add CAN controller chip. Increase board size. Re-route. Change oscillator footprint.
2020-02-27 final changes before ordering
2020-02-27 Organize schematic and documentation.
2020-02-27 Actually fix merge conflict.
2020-02-28 final fixes before ordering
2020-02-28 ordering, dimensions
2020-03-01 Design review changes part 2
2020-03-03 Final Changes to Fix Glaring issues
2020-03-04 temp hotswap reroute, not finished
2020-03-04 Labels, should be od
2020-03-05 Design review changes part 3
2020-03-05 Added TVS Diode
2020-03-08 Wire changes
2020-03-08 More work on Firmware
2020-03-12 CAN Addition
    Added the new CAN Controller. Routing on the board still needs to be done.
2020-03-13 3/1/2020
    Switched out CAN connector, cleaned up a few things
2020-03-13 Rounded Corners and Fixed wires
    Labels coming soon
2020-03-13 Finished Labels
    I follwed the style guide to get everything in place. I did labels and made the power plane 0.5 mm. The only problem might be that the connections are .15 mm thick.
2020-04-08 Adding system diagram
2020-04-15 4/14/20
    Added CAN Controller
2020-04-16 4/15/20
    Touched up board
2020-05-26 Complete except Firmware
2020-05-31 Spec sheet update
2020-06-13 Basic Updates Based on Notes
    Needs help with a few things but I will discuss them in meeting.
2020-06-20 Board Review Draft
2020-07-05 Core Edit Current Sensing
    Edited from core
2020-07-17 Initial commit, rigid body motion, rotation matrix, quaternion and special orthogonal group
2020-07-17 {IC, Sensor}.lbr changes from Estop-fix
2020-07-18 New Updates to Current Sensing
    Nearing final stages
2020-08-02 Translation, forward and inverse kinematics
2020-08-03 All libraries merged
2020-08-06 fixed xml file in igvc-connector redefinition, rip my git rebase
2020-08-06 Again, fixing xml files
2020-08-08 Fix underscore {} typo
2020-08-11 Add all place holders for math functions, added comments for arm configurations
2020-08-11 Add basic math functions
2020-08-13 Testing script for coordiante frame and jacobian
2020-08-19 Finalizing first edition of scripts
2020-08-19 Test scripts for inverse kinematics
2020-08-30 8/30/20
    Added to intro paragraph of main.tex
2020-10-02 Changes to Board Complete
    -Most recent round of commentes taken account of
2020-11-13 Current Sensing with Female resistor input
2020-11-26 SMD Resistor Update
2021-04-17 Logic Board
    Logic Board and Schematic
2021-10-17 Updated Oscillator
